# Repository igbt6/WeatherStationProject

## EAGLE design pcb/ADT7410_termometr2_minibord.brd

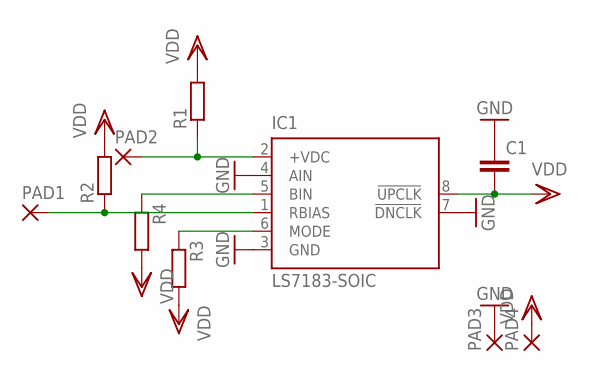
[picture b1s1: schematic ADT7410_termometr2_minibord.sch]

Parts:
C1: C-EUC0805; C0805
IC1: LS7183-SOIC; SOIC08
PAD1, PAD2, PAD3, PAD4: 1,6/0,8
R1, R2, R3, R4: R-EU_M0805; M0805

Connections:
GND: C1.1, IC1.3 (GND), IC1.4 (AIN), IC1.7 (!DNCLK), PAD3.1
unnamed: IC1.1 (RBIAS), PAD1.1, R2.1
unnamed: IC1.2 (+VDC), PAD2.1, R1.1
unnamed: IC1.5 (BIN), R4.1
unnamed: IC1.6 (MODE), R3.1
VDD: C1.2, IC1.8 (!UPCLK), PAD4.1, R1.2, R2.2, R3.2, R4.2

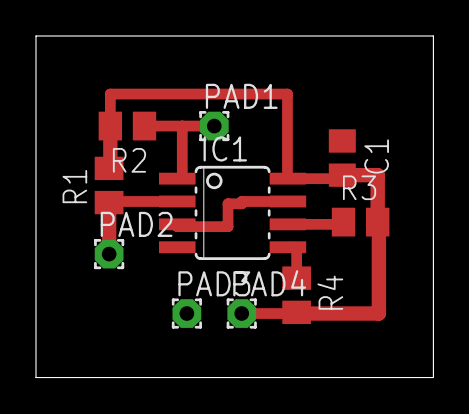
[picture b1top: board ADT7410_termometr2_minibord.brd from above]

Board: 2 copper layers, 22.1 x 19.0 mm, 10 parts (0 on the bottom side), 6 nets.

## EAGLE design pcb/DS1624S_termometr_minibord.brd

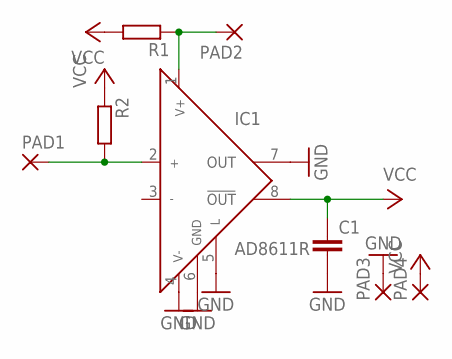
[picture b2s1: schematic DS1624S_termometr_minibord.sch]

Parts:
C1: C-EUC0805; C0805
IC1: AD8611R; SO8
PAD1, PAD2, PAD3, PAD4: 1,6/0,8
R1, R2: R-EU_M0805; M0805

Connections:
GND: C1.2, IC1.4 (V-), IC1.5 (L), IC1.6 (GND), IC1.7 (OUT), PAD3.1
unnamed: IC1.2 (IN+), PAD1.1, R2.2
unnamed: IC1.1 (V+), PAD2.1, R1.1
VCC: C1.1, IC1.8 (!OUT), PAD4.1, R1.2, R2.1

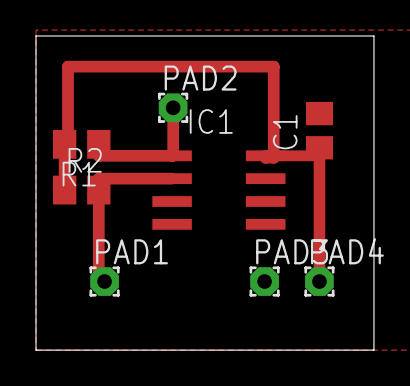
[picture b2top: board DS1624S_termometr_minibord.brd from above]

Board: 2 copper layers, 18.8 x 17.4 mm, 8 parts (0 on the bottom side), 4 nets.

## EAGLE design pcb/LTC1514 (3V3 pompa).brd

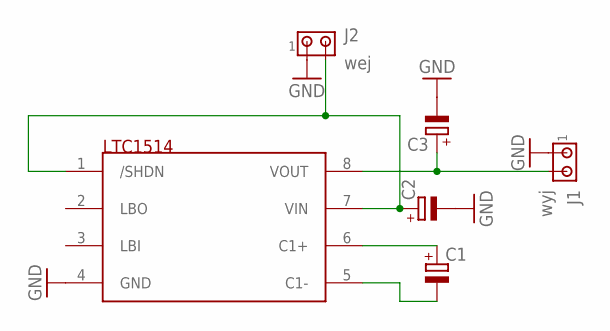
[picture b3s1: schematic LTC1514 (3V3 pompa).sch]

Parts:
C1, C2, C3: CPOL-EUE2,5-6E; E2,5-6E
J1: wyj; 10X02MTA
J2: wej; 10X02MTA
U$1: LTC1514; SO08

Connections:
GND: C2.-, C3.-, J1.1, J2.1, U$1.4 (GND)
unnamed: C2.+, J2.2, U$1.1 (/SHDN), U$1.7 (VIN)
unnamed: C1.+, U$1.6 (C1+)
unnamed: C1.-, U$1.5 (C1-)
unnamed: C3.+, J1.2, U$1.8 (VOUT)

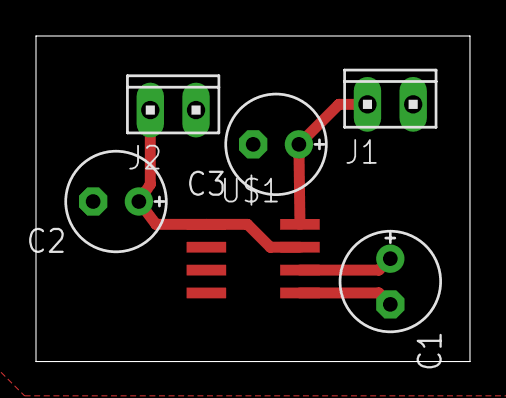
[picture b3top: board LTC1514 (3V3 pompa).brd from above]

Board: 2 copper layers, 24.1 x 18.1 mm, 6 parts (0 on the bottom side), 5 nets.

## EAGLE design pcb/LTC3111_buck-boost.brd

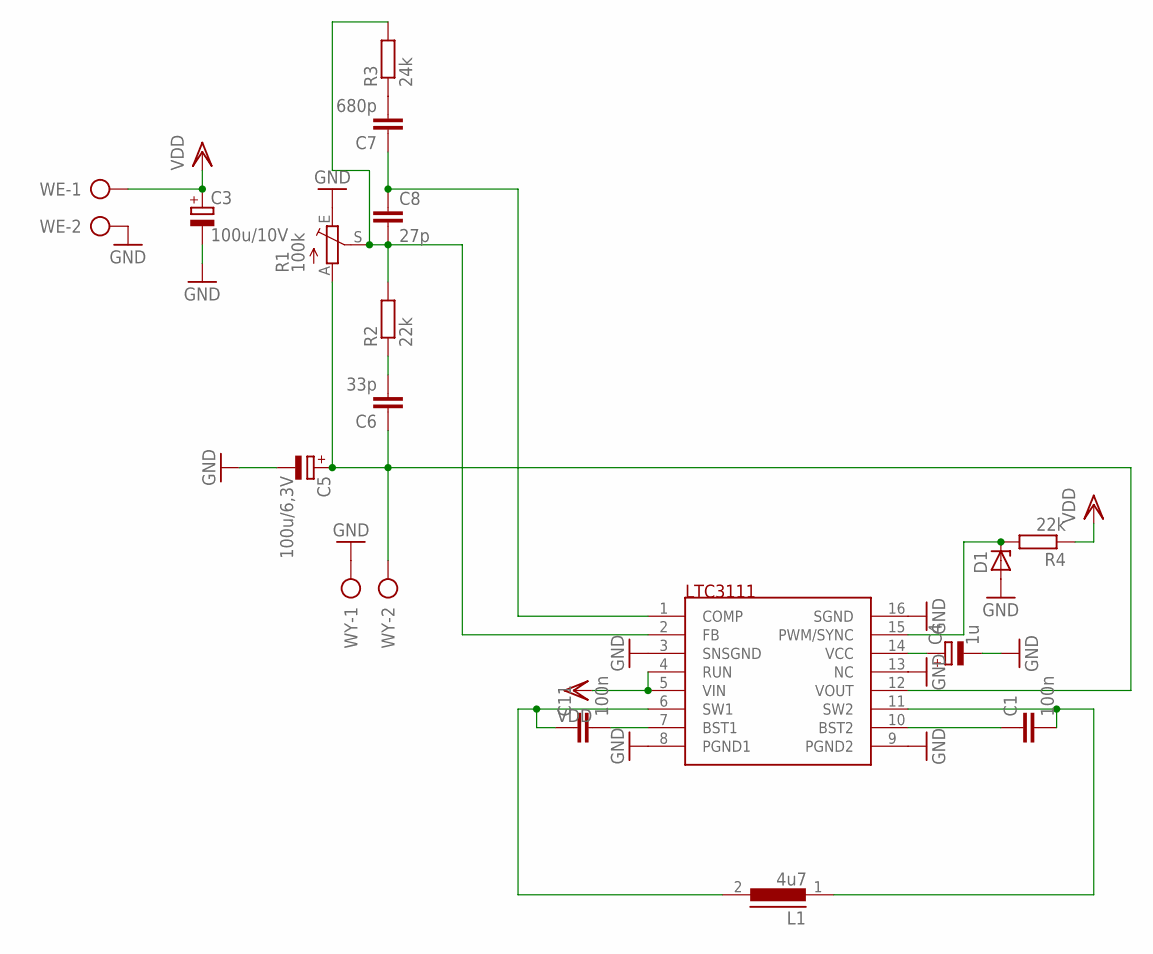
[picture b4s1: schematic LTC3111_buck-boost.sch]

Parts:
C1, C11: 100n; C0603K
C3: 100u/10V; E2,5-6
C4: 1u; E2,5-6
C5: 100u/6,3V; E2,5-7
C6: 33p; C0805
C7: 680p; C0805
C8: 27p; C0805
D1: ZENER-DIODESOD80C; SOD80C
L1: 4u7; DR73
R1: 100k; RJ9W
R2, R4: 22k; R0805
R3: 24k; R0805
U$2: LTC3111; MSOP16
WE: AK300/2
WY: AK300/2

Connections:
GND: C3.-, C4.-, C5.-, D1.A, R1.E, U$2.3 (SNSGND), U$2.8 (PGND1), U$2.9 (PGND2), U$2.13 (NC), U$2.16 (SGND), WE.2, WY.1
unnamed: C1.1, U$2.10 (BST2)
unnamed: C4.+, U$2.14 (VCC)
unnamed: C1.2, L1.1, U$2.11 (SW2)
unnamed: C6.2, R2.1
unnamed: C5.+, C6.1, R1.A, U$2.12 (VOUT), WY.2
unnamed: C8.2, R1.S, R2.2, R3.2, U$2.2 (FB)
unnamed: C7.2, R3.1
unnamed: C7.1, C8.1, U$2.1 (COMP)
unnamed: C11.1, L1.2, U$2.6 (SW1)
unnamed: C11.2, U$2.7 (BST1)
unnamed: D1.C, R4.2, U$2.15 (PWM/SYNC)
VDD: C3.+, R4.1, U$2.4 (RUN), U$2.5 (VIN), WE.1

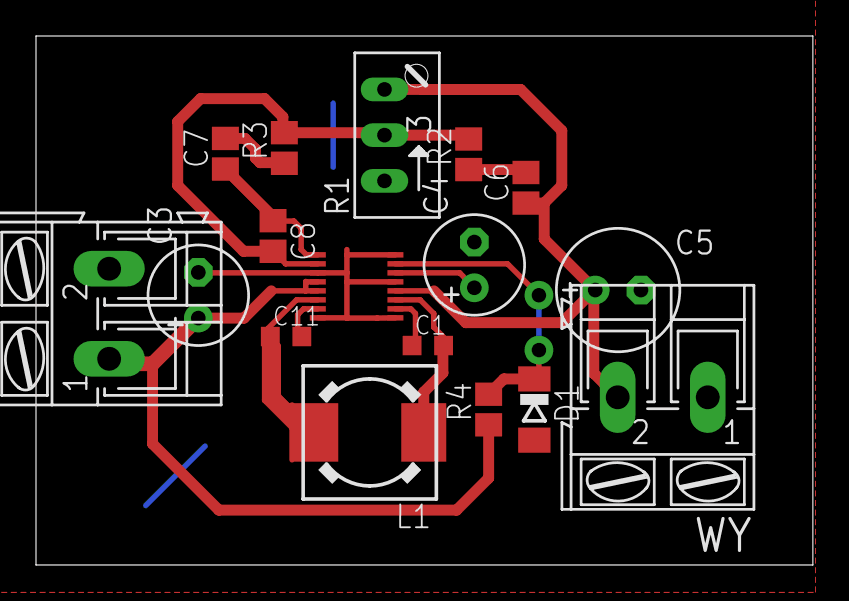
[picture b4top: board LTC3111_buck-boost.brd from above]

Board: 2 copper layers, 43.2 x 29.4 mm, 17 parts (0 on the bottom side), 13 nets.

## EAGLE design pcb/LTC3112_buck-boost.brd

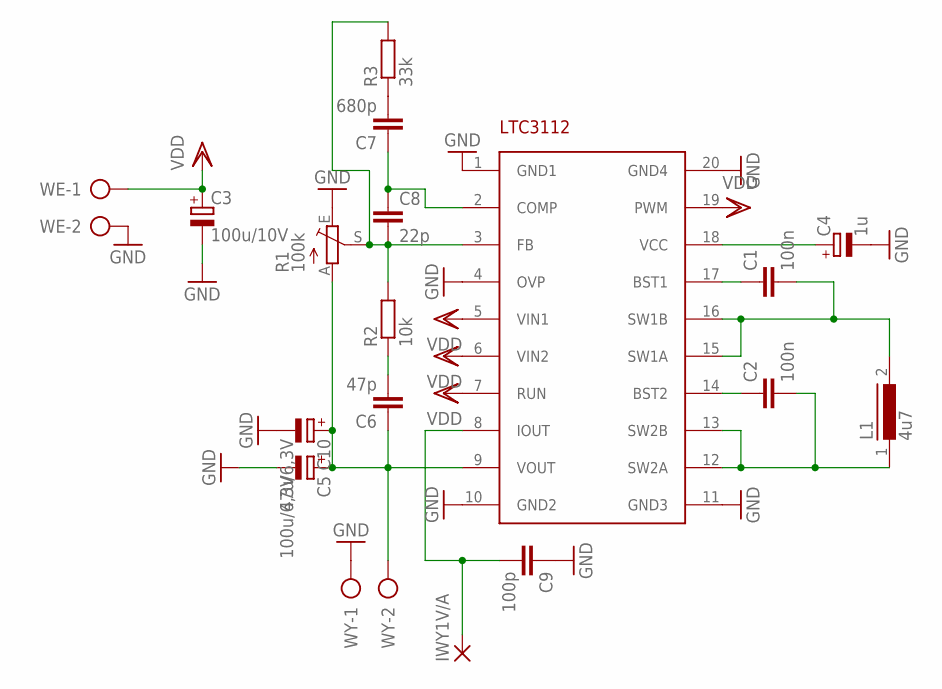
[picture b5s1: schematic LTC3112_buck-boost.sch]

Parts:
C1, C2: 100n; C0603K
C3: 100u/10V; E2,5-6
C4: 1u; SMC_B
C5: 100u/6,3V; E2,5-7
C6: 47p; C0805
C7: 680p; C0805
C8: 22p; C0805
C9: 100p; C0805
C10: 47u/6,3V; E1,8-4
IWY1V/A: 1,6/0,8
L1: 4u7; DR73
R1: 100k; RJ9W
R2: 10k; R0805
R3: 33k; R0805
U$1: LTC3112; TSSOP20
WE: AK300/2
WY: AK300/2

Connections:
GND: C3.-, C4.-, C5.-, C9.1, C10.-, R1.E, U$1.1 (GND1), U$1.4 (OVP), U$1.10 (GND2), U$1.11 (GND3), U$1.20 (GND4), WE.2, WY.1
unnamed: C1.1, U$1.17 (BST1)
unnamed: C2.1, U$1.14 (BST2)
unnamed: C1.2, L1.2, U$1.15 (SW1A), U$1.16 (SW1B)
unnamed: C4.+, U$1.18 (VCC)
unnamed: C6.2, R2.1
unnamed: C5.+, C6.1, C10.+, R1.A, U$1.9 (VOUT), WY.2
unnamed: C8.2, R1.S, R2.2, R3.2, U$1.3 (FB)
unnamed: C7.2, R3.1
unnamed: C7.1, C8.1, U$1.2 (COMP)
unnamed: C9.2, IWY1V/A.1, U$1.8 (IOUT)
unnamed: C2.2, L1.1, U$1.12 (SW2A), U$1.13 (SW2B)
VDD: C3.+, U$1.5 (VIN1), U$1.6 (VIN2), U$1.7 (RUN), U$1.19 (PWM), WE.1

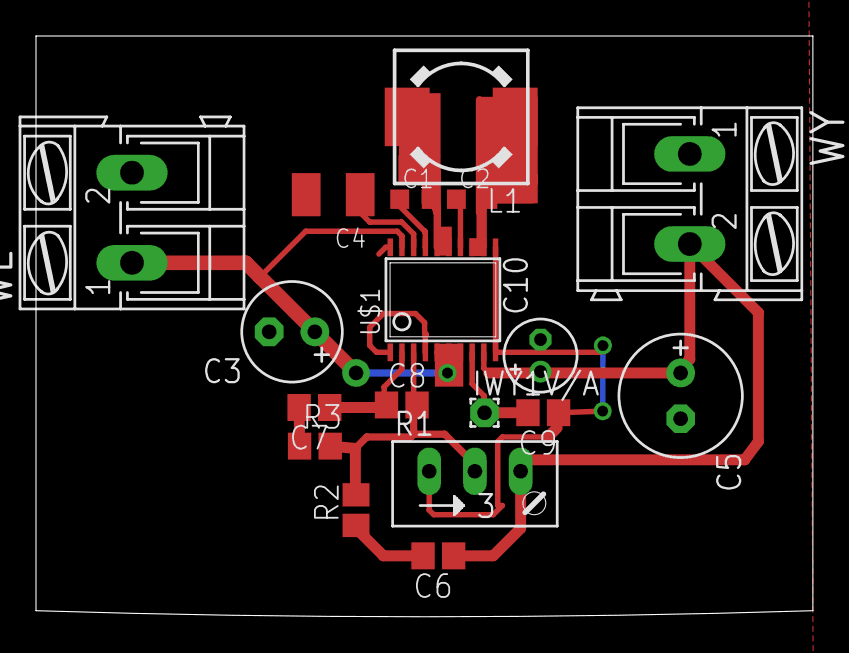
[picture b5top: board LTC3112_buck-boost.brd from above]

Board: 2 copper layers, 43.2 x 32.3 mm, 18 parts (0 on the bottom side), 13 nets.

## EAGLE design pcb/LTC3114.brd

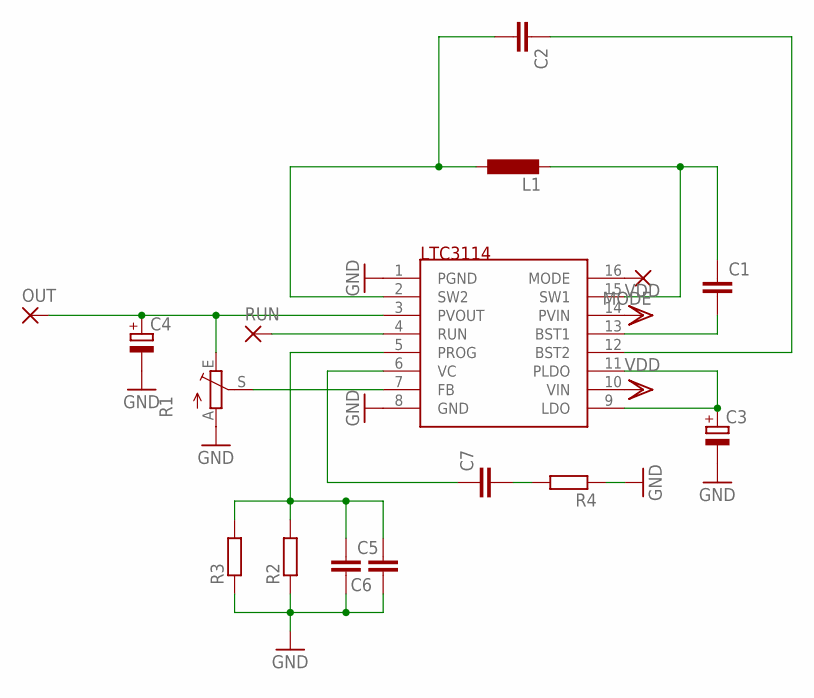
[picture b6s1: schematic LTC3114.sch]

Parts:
C1, C2, C5, C7: C-EUC0805; C0805
C3, C4: CPOL-EUE2,5-6E; E2,5-6E
C6: C-EU025-025X050; C025-025X050
L1: L-EUL3225M; L3225M
MODE: 1,6/0,8
OUT: 1,6/0,8
R1: TRIM_EU-RJ9W; RJ9W
R2, R4: R-EU_M0805; M0805
R3: R-EU_0204/7; 0204/7
RUN: 1,6/0,8
U$1: LTC3114; TSSOP16

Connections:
GND: C3.-, C4.-, C5.2, C6.1, R1.A, R2.1, R3.1, R4.1, U$1.1 (PGND), U$1.8 (GND)
unnamed: C1.2, U$1.13 (BST1)
unnamed: C1.1, L1.2, U$1.15 (SW1)
unnamed: C2.1, U$1.12 (BST2)
unnamed: C2.2, L1.1, U$1.2 (SW2)
unnamed: C3.+, U$1.9 (LDO), U$1.11 (PLDO)
unnamed: R1.S, U$1.7 (FB)
unnamed: C4.+, OUT.1, R1.E, U$1.3 (PVOUT)
unnamed: RUN.1, U$1.4 (RUN)
unnamed: C5.1, C6.2, R2.2, R3.2, U$1.5 (PROG)
unnamed: MODE.1, U$1.16 (MODE)
unnamed: C7.2, R4.2
unnamed: C7.1, U$1.6 (VC)
VDD: U$1.10 (VIN), U$1.14 (PVIN)

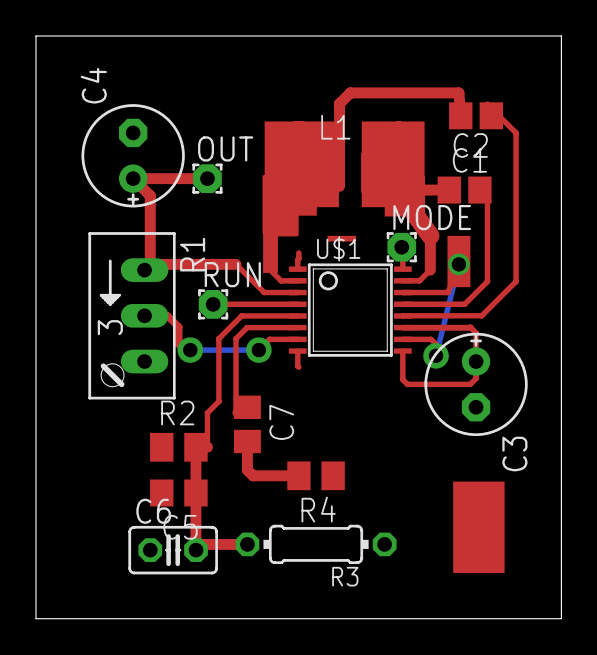
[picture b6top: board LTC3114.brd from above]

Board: 2 copper layers, 29.2 x 32.4 mm, 16 parts (0 on the bottom side), 14 nets.

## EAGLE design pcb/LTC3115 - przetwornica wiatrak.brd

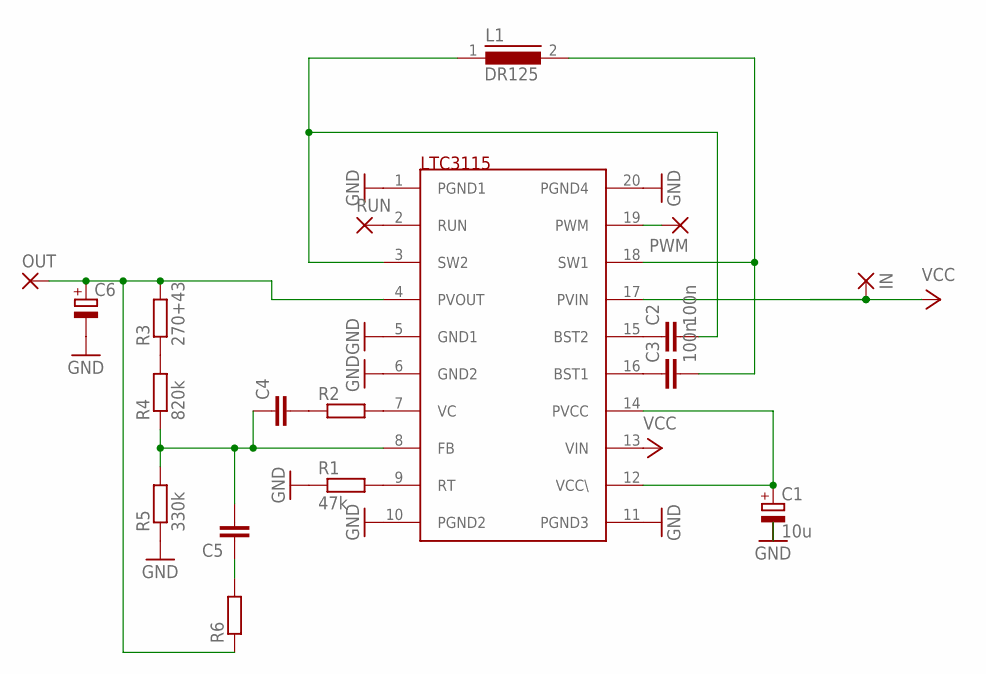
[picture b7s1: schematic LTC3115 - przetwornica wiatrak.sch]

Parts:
C1: 10u; E2,5-7
C2, C3: 100n; C0805
C4, C5: C-EUC0805; C0805
C6: CPOL-EUE3.5-8; E3,5-8
IN: 2,54/0,9
L1: DR125
OUT: 2,54/0,9
PWM: 2,54/0,9
R1: 47k; R0805
R2, R6: R-EU_R0805; R0805
R3: 270+43; R0805
R4: 820k; R0805
R5: 330k; R0805
RUN: 2,54/0,9
U$1: LTC3115; TSSOP20

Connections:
GND: C1.-, C6.-, R1.1, R5.1, U$1.1 (PGND1), U$1.5 (GND1), U$1.6 (GND2), U$1.10 (PGND2), U$1.11 (PGND3), U$1.20 (PGND4)
unnamed: C1.+, U$1.12 (VCC\), U$1.14 (PVCC)
unnamed: R1.2, U$1.9 (RT)
unnamed: R2.2, U$1.7 (VC)
unnamed: C4.1, C5.2, R4.1, R5.2, U$1.8 (FB)
unnamed: R3.1, R4.2
unnamed: C6.+, OUT.1, R3.2, R6.1, U$1.4 (PVOUT)
unnamed: C2.1, U$1.15 (BST2)
unnamed: C3.1, U$1.16 (BST1)
unnamed: C4.2, R2.1
unnamed: PWM.1, U$1.19 (PWM)
unnamed: RUN.1, U$1.2 (RUN)
unnamed: C2.2, L1.1, U$1.3 (SW2)
unnamed: C3.2, L1.2, U$1.18 (SW1)
unnamed: C5.1, R6.2
VCC: IN.1, U$1.13 (VIN), U$1.17 (PVIN)

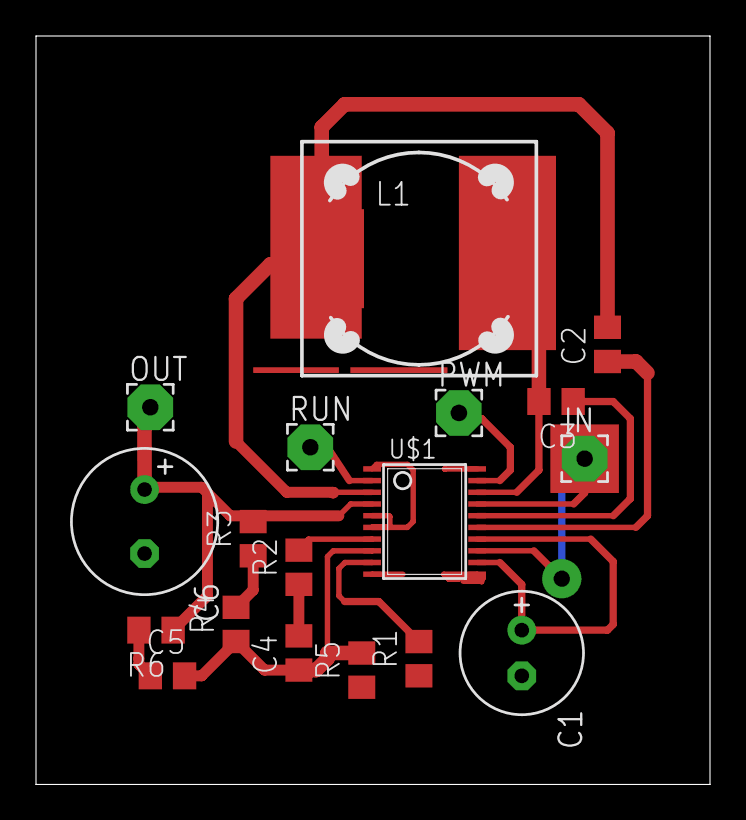
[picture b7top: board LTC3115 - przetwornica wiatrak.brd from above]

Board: 2 copper layers, 37.4 x 41.6 mm, 18 parts (0 on the bottom side), 16 nets.

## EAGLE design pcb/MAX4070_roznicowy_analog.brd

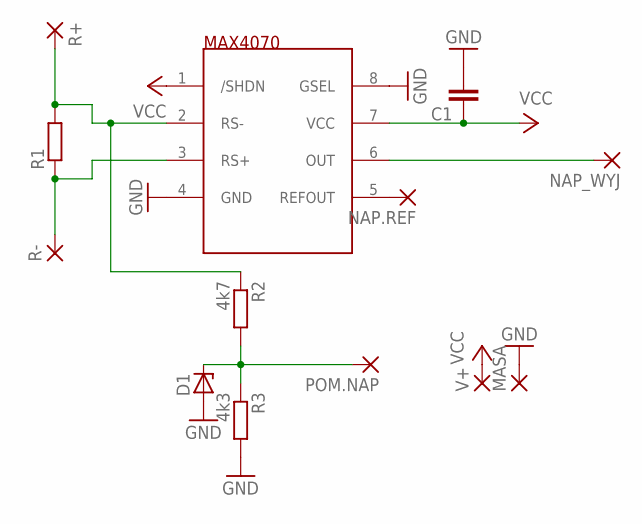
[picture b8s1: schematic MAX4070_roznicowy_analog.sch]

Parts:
C1: C-EUC1206; C1206
D1: ZENER-DIODESOD80C; SOD80C
MASA: 1,6/0,8
NAP.REF: 1,6/0,8
NAP_WYJ: 1,6/0,8
POM.NAP: 1,6/0,8
R1: R-EU_0617/22; 0617/22
R2: 4k7; 0207/10
R3: 4k3; 0207/10
R+: 1,6/0,8
R-: 1,6/0,8
U$1: MAX4070; UMAX8
V+: 1,6/0,8

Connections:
GND: C1.2, D1.A, MASA.1, R3.2, U$1.4 (GND), U$1.8 (GSEL)
unnamed: NAP_WYJ.1, U$1.6 (OUT)
unnamed: NAP.REF.1, U$1.5 (REFOUT)
unnamed: R1.2, R2.1, R+.1, U$1.2 (RS-)
unnamed: D1.C, POM.NAP.1, R2.2, R3.1
unnamed: R1.1, R-.1, U$1.3 (RS+)
VCC: C1.1, U$1.1 (/SHDN), U$1.7 (VCC), V+.1

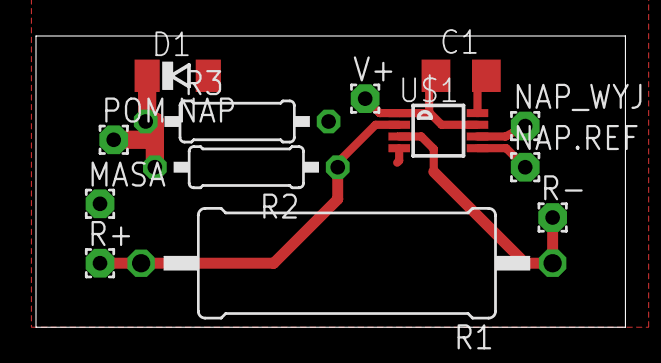
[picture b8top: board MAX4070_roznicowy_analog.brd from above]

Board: 2 copper layers, 32.7 x 16.2 mm, 13 parts (0 on the bottom side), 7 nets.
